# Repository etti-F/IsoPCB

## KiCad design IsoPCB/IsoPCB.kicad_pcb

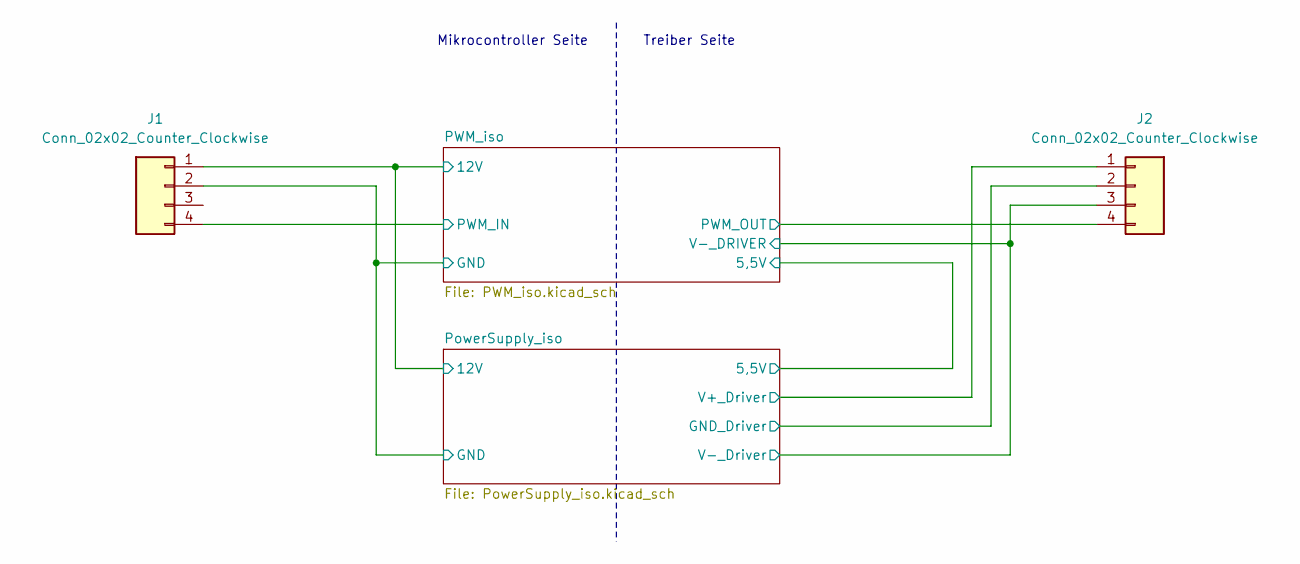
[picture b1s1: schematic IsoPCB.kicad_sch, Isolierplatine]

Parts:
J1: Conn_02x02_Counter_Clockwise; PinHeader_2x02_P2.54mm_Horizontal
J2: Conn_02x02_Counter_Clockwise; PinSocket_2x02_P2.54mm_Horizontal

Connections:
+12V: J1.1; also elsewhere on the board
/PWM_iso/PWM_IN: J1.4; also elsewhere on the board
/PWM_iso/PWM_OUT: J2.4; also elsewhere on the board
/PWM_iso/V-_DRIVER: J2.3; also elsewhere on the board
/PowerSupply_iso/V+_Driver: J2.1; also elsewhere on the board
GND: J1.2; also elsewhere on the board
GND_Driver: J2.2; also elsewhere on the board

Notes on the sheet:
Treiber Seite
Mikrocontroller Seite

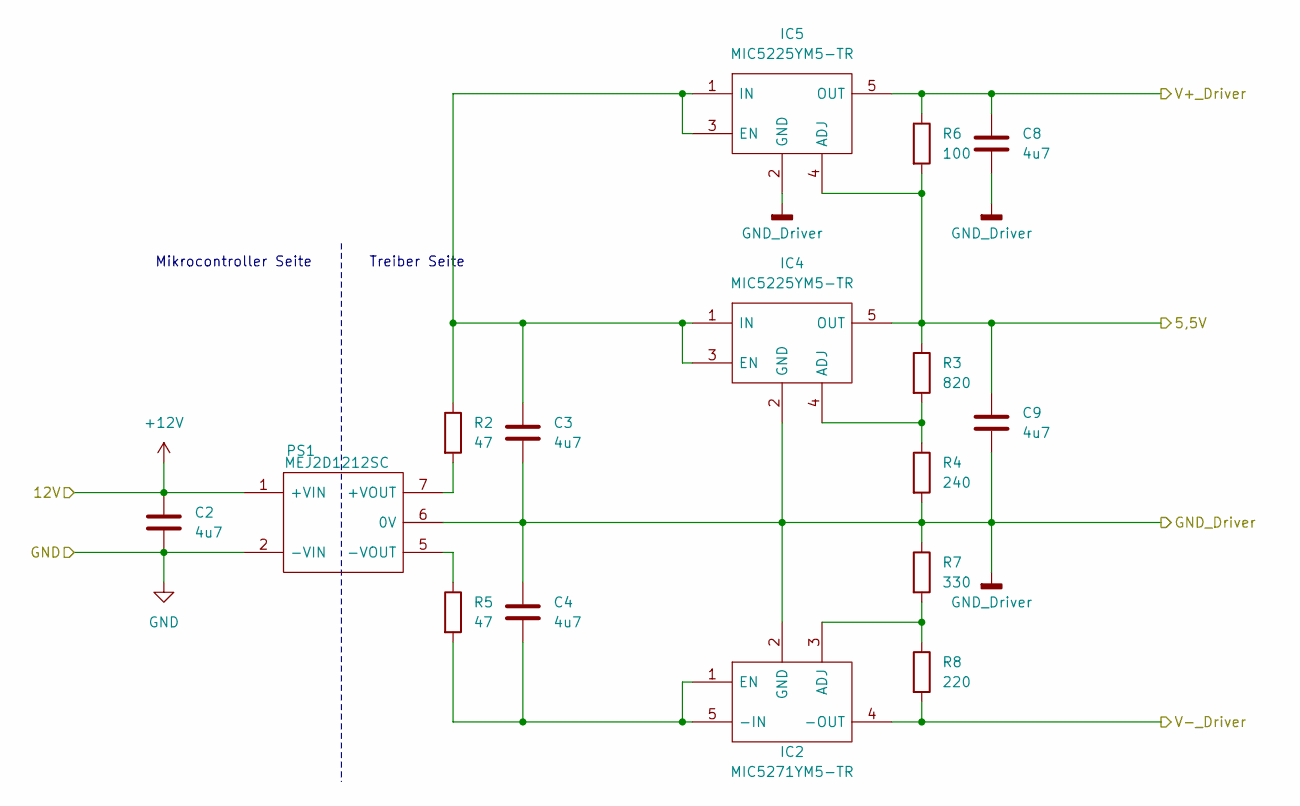
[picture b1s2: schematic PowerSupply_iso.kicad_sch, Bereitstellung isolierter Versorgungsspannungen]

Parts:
C2, C3, C4, C8, C9: 4u7; C_0805_2012Metric
IC2: MIC5271YM5-TR; SOT95P280X145-5N; Manufacturer_Part_Number MIC5271YM5-TR; Mouser Part Number 998-MIC5271YM5TR
IC4, IC5: MIC5225YM5-TR; SOT95P280X145-5N; Manufacturer_Part_Number MIC5225YM5-TR; Mouser Part Number 998-MIC5225YM5TR
PS1: MEJ2D1212SC; Manufacturer_Part_Number MEJ2D1212SC; Mouser Part Number 580-MEJ2D1212SC
R2, R5: 47; R_0603_1608Metric
R3: 820; R_0603_1608Metric
R4: 240; R_0603_1608Metric
R6: 100; R_0603_1608Metric
R7: 330; R_0603_1608Metric
R8: 220; R_0603_1608Metric

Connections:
+12V: C2.1, PS1.1 (+VIN); also elsewhere on the board
/PWM_iso/5,5V: C9.1, IC4.5 (OUT), IC5.4 (ADJ), R3.1, R6.2; also elsewhere on the board
/PWM_iso/V-_DRIVER: IC2.4 (-OUT), R8.2; also elsewhere on the board
/PowerSupply_iso/V+_Driver: C8.1, IC5.5 (OUT), R6.1; also elsewhere on the board
GND: C2.2, PS1.2 (-VIN); also elsewhere on the board
GND_Driver: C3.2, C4.1, C8.2, C9.2, IC2.2 (GND), IC4.2 (GND), IC5.2 (GND), PS1.6 (0V), R4.2, R7.1; also elsewhere on the board
unnamed: C4.2, IC2.1 (EN), IC2.5 (-IN), R5.2
unnamed: IC2.3 (ADJ), R7.2, R8.1
unnamed: IC4.4 (ADJ), R3.2, R4.1
unnamed: C3.1, IC4.1 (IN), IC4.3 (EN), IC5.1 (IN), IC5.3 (EN), R2.1
unnamed: PS1.7 (+VOUT), R2.2
unnamed: PS1.5 (-VOUT), R5.1

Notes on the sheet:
Treiber Seite
Mikrocontroller Seite

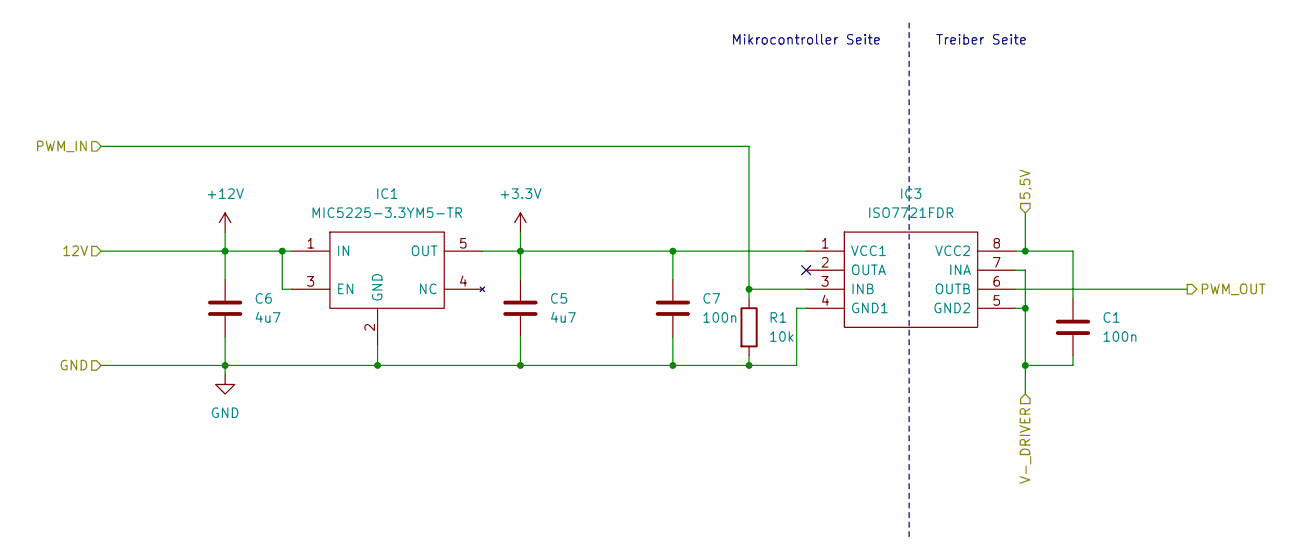
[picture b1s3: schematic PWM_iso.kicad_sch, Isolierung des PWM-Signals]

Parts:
C1, C7: 100n; C_0603_1608Metric
C5, C6: 4u7; C_0805_2012Metric
IC1: MIC5225-3.3YM5-TR; SOT95P280X145-5N; Manufacturer_Part_Number MIC5225-3.3YM5-TR; Mouser Part Number 998-MIC5225-3.3YM5TR
IC3: ISO7721FDR; SOIC127P600X175-8N; Manufacturer_Part_Number ISO7721FDR; Mouser Part Number 595-ISO7721FDR
R1: 10k; R_0603_1608Metric

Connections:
+3.3V: C5.1, C7.1, IC1.5 (OUT), IC3.1 (VCC1)
+12V: C6.1, IC1.1 (IN), IC1.3 (EN); also elsewhere on the board
/PWM_iso/5,5V: C1.1, IC3.8 (VCC2); also elsewhere on the board
/PWM_iso/PWM_IN: IC3.3 (INB), R1.1; also elsewhere on the board
/PWM_iso/PWM_OUT: IC3.6 (OUTB); also elsewhere on the board
/PWM_iso/V-_DRIVER: C1.2, IC3.5 (GND2), IC3.7 (INA); also elsewhere on the board
GND: C5.2, C6.2, C7.2, IC1.2 (GND), IC3.4 (GND1), R1.2; also elsewhere on the board

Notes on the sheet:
Mikrocontroller Seite
Treiber Seite

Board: 2 copper layers, 25 parts (0 on the bottom side), 15 nets, no tracks yet.

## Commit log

2025-06-04 Dateien angelegt
2025-06-05 Bauteile eingepflegt und Schaltplan erstellt
